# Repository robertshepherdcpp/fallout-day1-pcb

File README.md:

# fallout-day1-pcb
a pcb i made for the first day in fallout

a pcb in the shape of a pig which u can pet!

slack: @rshepherdcpp

- a project to have ur own pet keychain
- that is just a pcb
- powered by a coin sized battery
- keep ur pet happy by touching the ear on the correct side (dont do it on the wrong side else hell get angry!)

BOM image:

code: to do!

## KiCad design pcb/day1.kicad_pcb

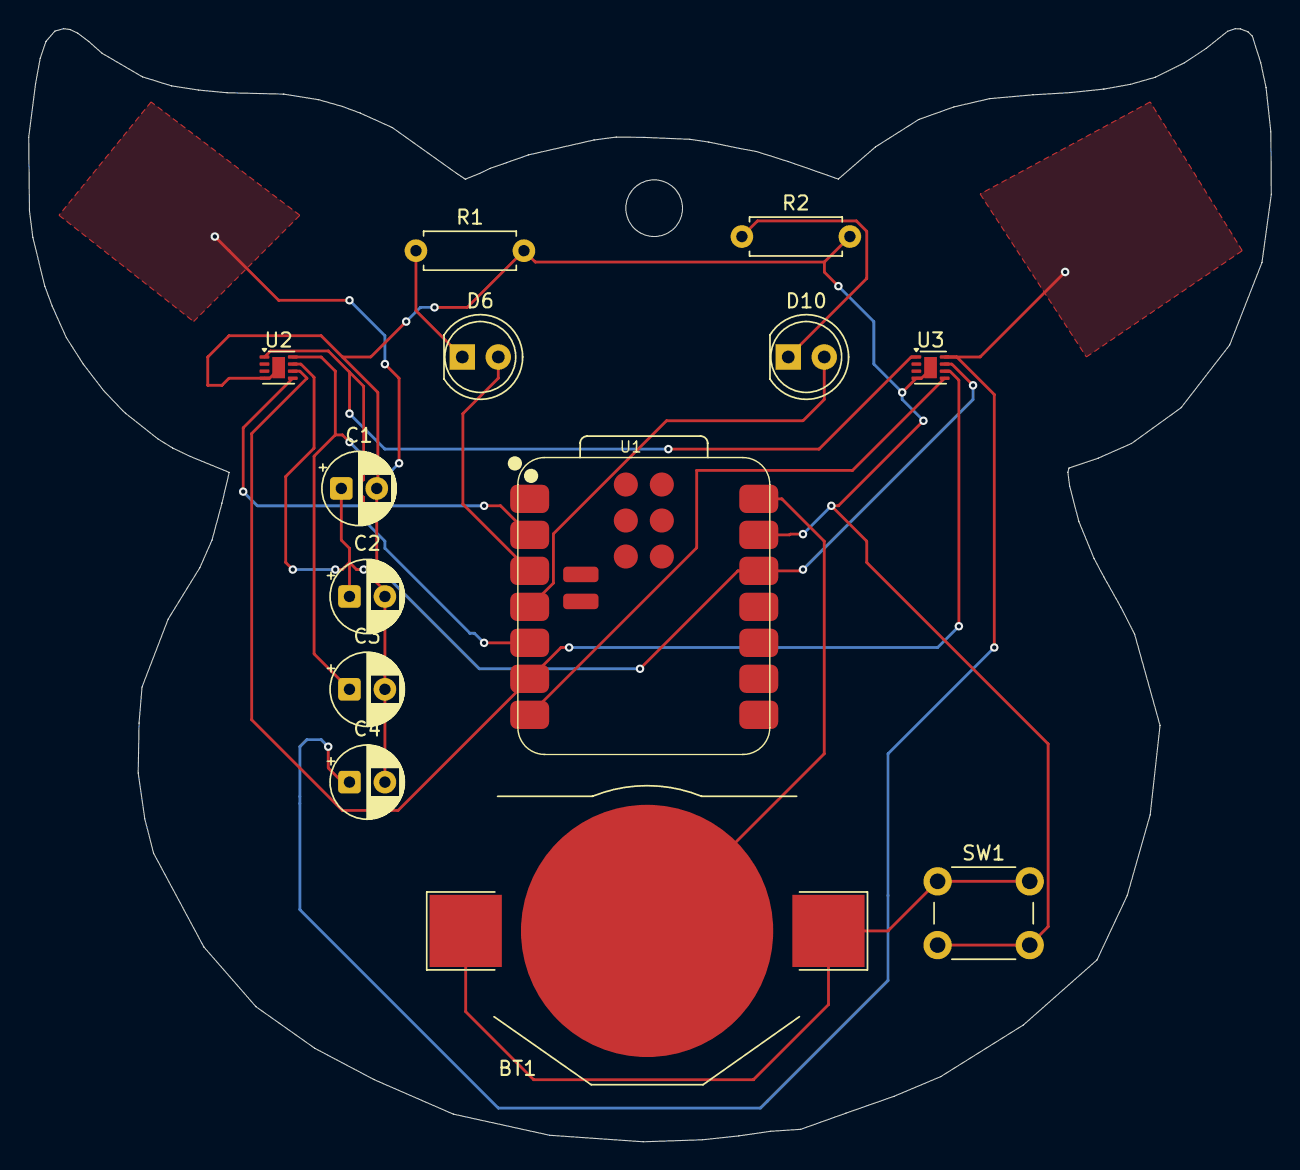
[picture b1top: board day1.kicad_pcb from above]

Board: 2 copper layers, 87.7 x 78.5 mm, 13 parts (0 on the bottom side), 14 nets.

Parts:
BT1: Battery; BatteryHolder_Keystone_3002_1x2032
C1, C2: 0.1uF; CP_Radial_D5.0mm_P2.50mm
C3, C4: 2.7nF; CP_Radial_D5.0mm_P2.50mm
D6, D10: LED; LED_D5.0mm
R1, R2: 470; R_Axial_DIN0207_L6.3mm_D2.5mm_P7.62mm_Horizontal
SW1: SW_Push; SW_PUSH_6mm
U1: XIAO-ESP32-C3-SMD
U2, U3: AT42QT1010-M; DFN-8-1EP_2x2mm_P0.5mm_EP0.9x1.5mm

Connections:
3.3v: C1.1, C2.1, U1.12 (3V3), U2.7 (VDD), U3.7 (VDD)
GND: C1.2, C2.2, C3.2, C4.2, R1.2, R2.2, SW1.2, U1.13 (GND), U2.4 (VSS), U2.9 (VSS), U3.4 (VSS), U3.9 (VSS)
LED1: D6.2 (A), U1.3 (GPIO4_A2_D2)
LED2: D10.2 (A), U1.4 (GPIO5_A3_D3)
unnamed: BT1.1 (+), SW1.1
unnamed: BT1.2 (-), U1.14 (VBUS)
unnamed: D6.1 (K), R1.1
unnamed: D10.1 (K), R2.1
OUT1: U1.2 (GPIO3_A1_D1), U2.5 (OUT)
OUT2: U1.7 (GPIO21_D6_TX), U3.5 (OUT)
SCL: U1.6 (GPIO7_D5_SCL), U2.6 (SYNC), U3.6 (SYNC)
SDA: U1.5 (GPIO6_D4_SDA), U2.1 (SNSK), U3.1 (SNSK)
SNS1: C3.1, U2.8 (SNS)
SNS2: C4.1, U3.8 (SNS)
